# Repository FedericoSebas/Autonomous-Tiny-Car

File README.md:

# Self-Driving Car Project

Hello there, this project is now in v1.0.0. We have developed the initial idea and made significant progress.

## Project Overview

This project is about a self-driving car that uses a PC and an ESP32CAM mounted on a tiny car. The video from the ESP32CAM is processed on the PC using Python, NumPy, and OpenCV to measure the curve of a path. The curve data is then sent to a MQTT broker, which forwards it to the ESP32CAM. The ESP32CAM uses this curve data to control the car's movement using a PID system.

## Key Files

The main logic of the project is contained in two files:

1. `./src-arduino/src/sketch.cpp` lines 1225 to 1242: This part of the code handles the communication with the MQTT broker and the processing of the curve data.

2. `./src-arduino/src/Motor.cpp` lines 40 to 87: This part of the code controls the movement of the car based on the curve data. It uses a PID system to adjust the car's speed and direction based on the curve of the path. After moving the motors, there is a microsecond delay before returning the curve and turn values.

## Requirements

If you want to upload the code to your ESP32CAM, you need to use PlatformIO and be in the ./src-arduino directory. Then, type `pio run` in the command line. This will download all the necessary libraries. After that, type `pio -t upload`, and it will upload the code to your ESP32CAM. If you are not comfortable with PlatformIO, you can extract the entire src-arduino folder and use it in Arduino. Please note that you might need to adjust the library paths in your code if you move it to a different location.

## Future Updates

We are continuously working on improving this project. Stay tuned for future updates!

## Illustrative Content

https://github.com/FedericoSebas/CERTERO-Smart-Car/assets/108437899/04f8dd56-40b6-4fee-bdeb-6901cfbc2fd8

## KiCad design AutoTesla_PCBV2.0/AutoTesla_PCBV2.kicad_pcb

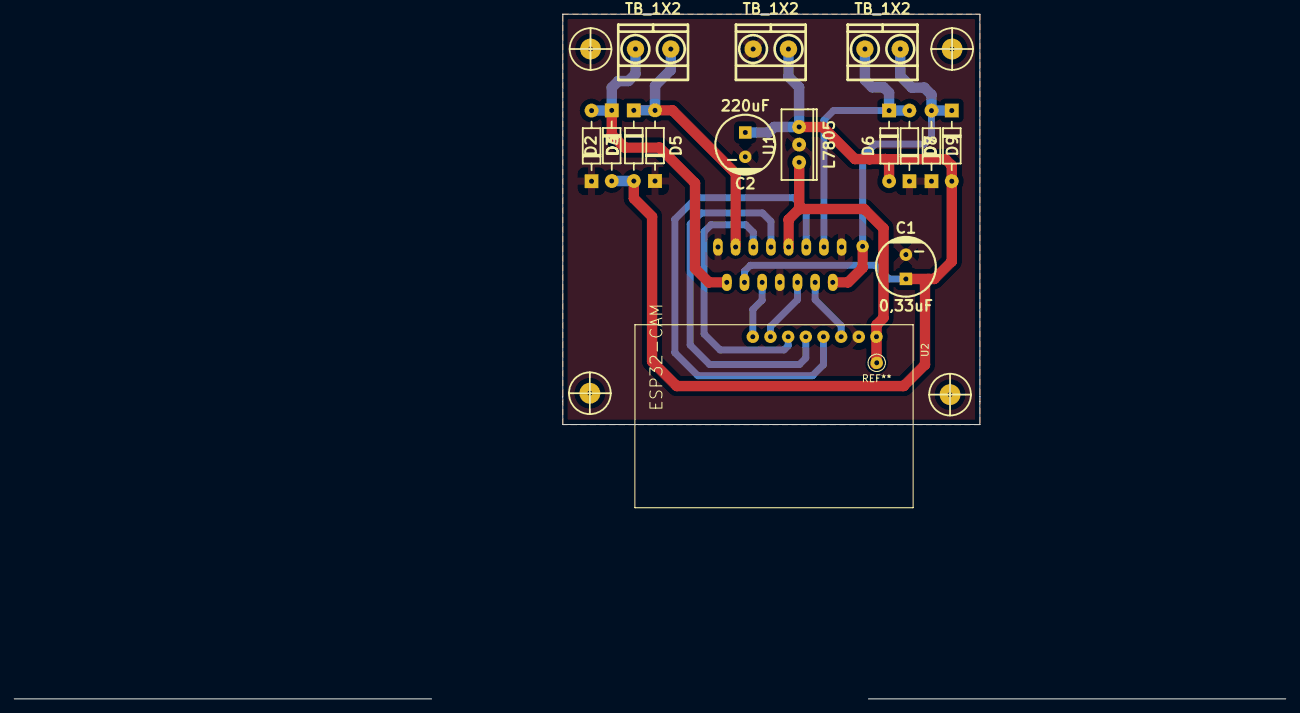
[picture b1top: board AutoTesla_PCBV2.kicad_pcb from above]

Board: 2 copper layers, 60.0 x 59.0 mm, 20 parts (1 on the bottom side), 13 nets.

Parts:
C1: 0,33uF; CAP_ELEC_8x11.5mm
C2: 220uF; CAP_ELEC_8x11.5mm
D2, D3, D4, D5, D6, D7, D8, D9: D; DO-41
H1, H2, H3, H4: Mounting_Hole; hole_3mm
J1, J2, J3: TB_1X2; BORNERA2_AZUL
U1: L7805; TO-220
U2: ESP32-CAM
U3: L298HN; TO127P2020X500X2100-15

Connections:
+5V: U1.3 (OUT), U2.P$1 (5V), U3.9 (Vss)
+6V: C1.1, C2.1, D2.1 (K), D4.1 (K), D6.1 (K), D8.1 (K), J1.1, U1.1 (IN), U3.4 (Vs)
/EnA: U2.P$8 (IO4), U3.6 (EnA)
/EnB: U2.P$4 (IO13), U3.11 (EnB)
/IN1: U2.P$6 (IO14), U3.5 (IN1)
/IN2: U2.P$5 (IO15), U3.7 (IN2)
/IN3: U2.P$7 (IO2), U3.10 (IN3)
/IN4: U2.P$3 (IO12), U3.12 (IN4)
/OUT1: D2.2 (A), D3.1 (K), J3.2, U3.2 (OUT1)
/OUT2: D4.2 (A), D5.1 (K), J3.1, U3.3 (OUT2)
/OUT3: D6.2 (A), D7.1 (K), J2.2, U3.13 (OUT3)
/OUT4: D8.2 (A), D9.1 (K), J2.1, U3.14 (OUT4)
GND: C1.2, C2.2, D3.2 (A), D5.2 (A), D7.2 (A), D9.2 (A), J1.2, U1.2 (GND), U2.P$2 (GND), U3.1 (SENSE_A), U3.8 (GND), U3.15 (SENSE_B)

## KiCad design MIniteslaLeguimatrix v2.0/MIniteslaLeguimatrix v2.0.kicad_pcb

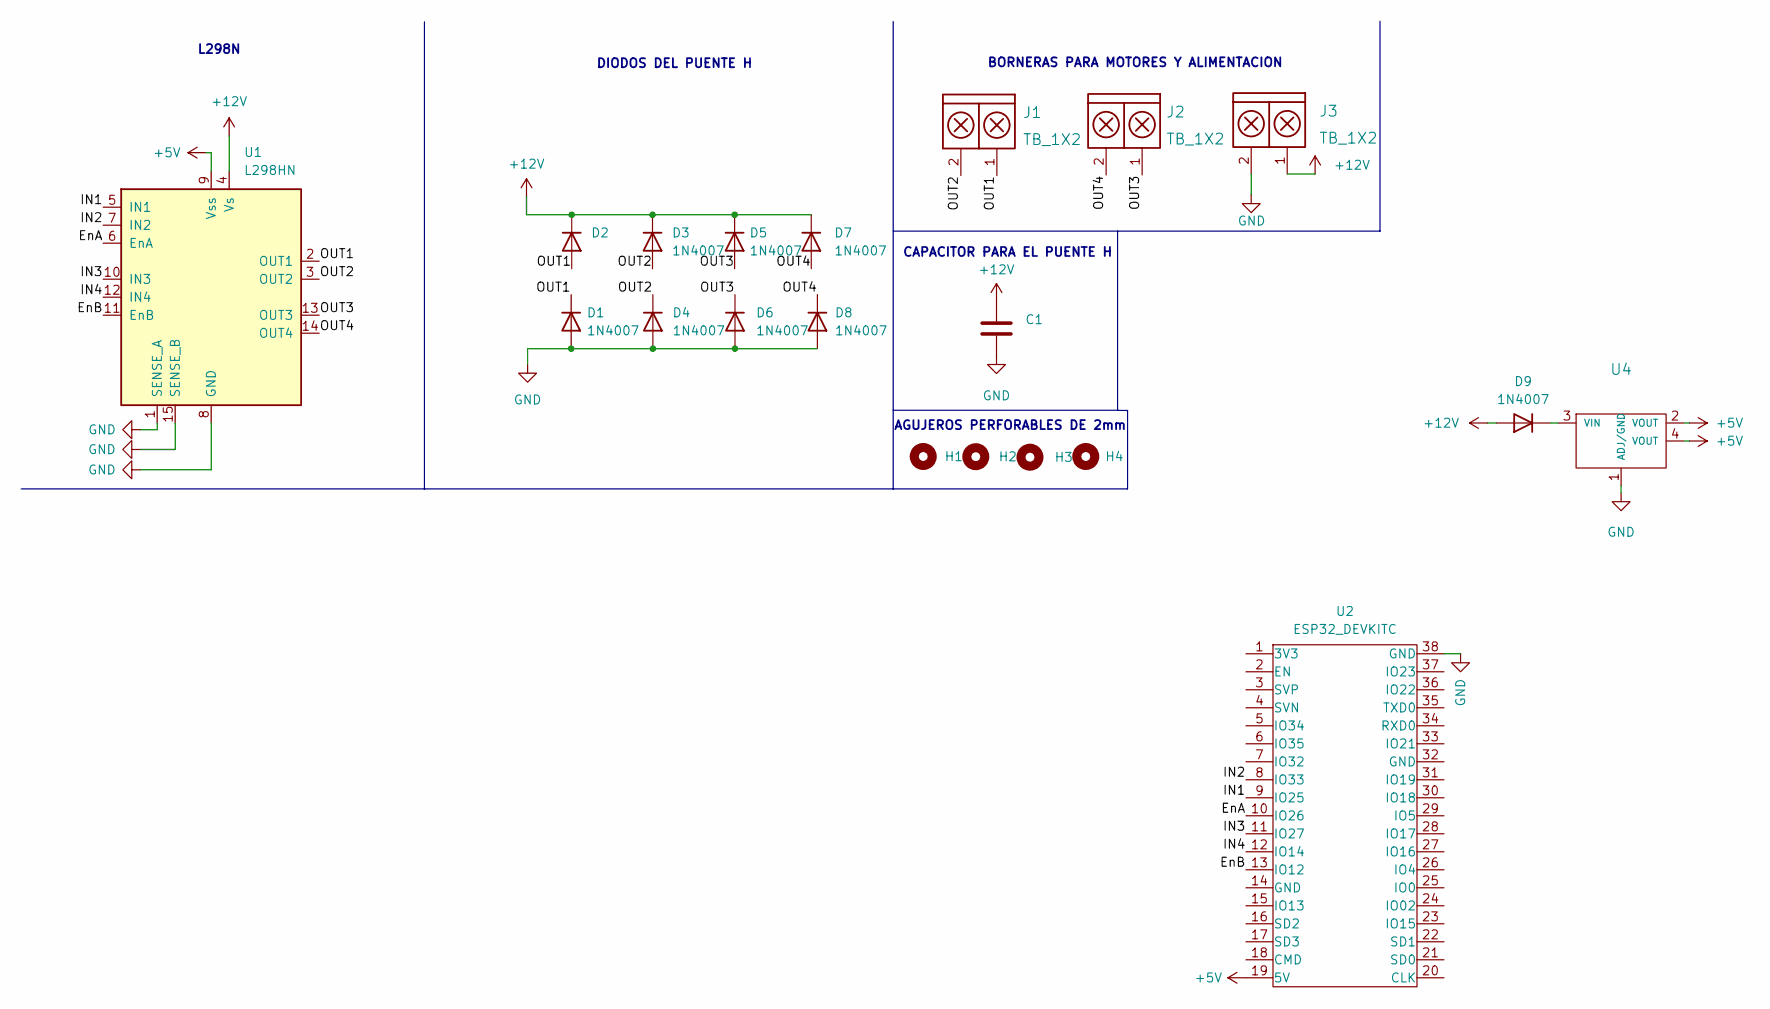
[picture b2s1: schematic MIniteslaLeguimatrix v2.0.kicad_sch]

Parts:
C1: (no value)
D1, D3, D4, D5, D6, D7, D8, D9: 1N4007
D2: (no value)
H1, H2, H3, H4: Mounting_Hole; Tornillo_M3_8mm
J1, J2, J3: TB_1X2; BORNERA2_AZUL
U1: L298HN; TO-220-15_P2.54x2.54mm_StaggerOdd_Lead4.58mm_Vertical
U2: ESP32_DEVKITC
U4: (no value)

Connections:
+5V: U1.9 (Vss), U2.19 (5V), U4.2 (VOUT), U4.4 (VOUT)
+12V: C1.1, D2.1 (K), D3.1 (K), D5.1 (K), D7.1 (K), D9.2 (A), J3.1, U1.4 (Vs)
/EnA: U1.6 (EnA), U2.10 (IO26)
/EnB: U1.11 (EnB), U2.13 (IO12)
/IN1: U1.5 (IN1), U2.9 (IO25)
/IN2: U1.7 (IN2), U2.8 (IO33)
/IN3: U1.10 (IN3), U2.11 (IO27)
/IN4: U1.12 (IN4), U2.12 (IO14)
/OUT1: D1.1 (K), D2.2 (A), J1.1, U1.2 (OUT1)
/OUT2: D3.2 (A), D4.1 (K), J1.2, U1.3 (OUT2)
/OUT3: D5.2 (A), D6.1 (K), J2.1, U1.13 (OUT3)
/OUT4: D7.2 (A), D8.1 (K), J2.2, U1.14 (OUT4)
GND: C1.2, D1.2 (A), D4.2 (A), D6.2 (A), D8.2 (A), J3.2, U1.1 (SENSE_A), U1.8 (GND), U1.15 (SENSE_B), U2.38 (GND), U4.1 (ADJ/GND)
unnamed: D9.1 (K), U4.3 (VIN)

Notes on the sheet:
L298N
DIODOS DEL PUENTE H
BORNERAS PARA MOTORES Y ALIMENTACION
AGUJEROS PERFORABLES DE 2mm
CAPACITOR PARA EL PUENTE H

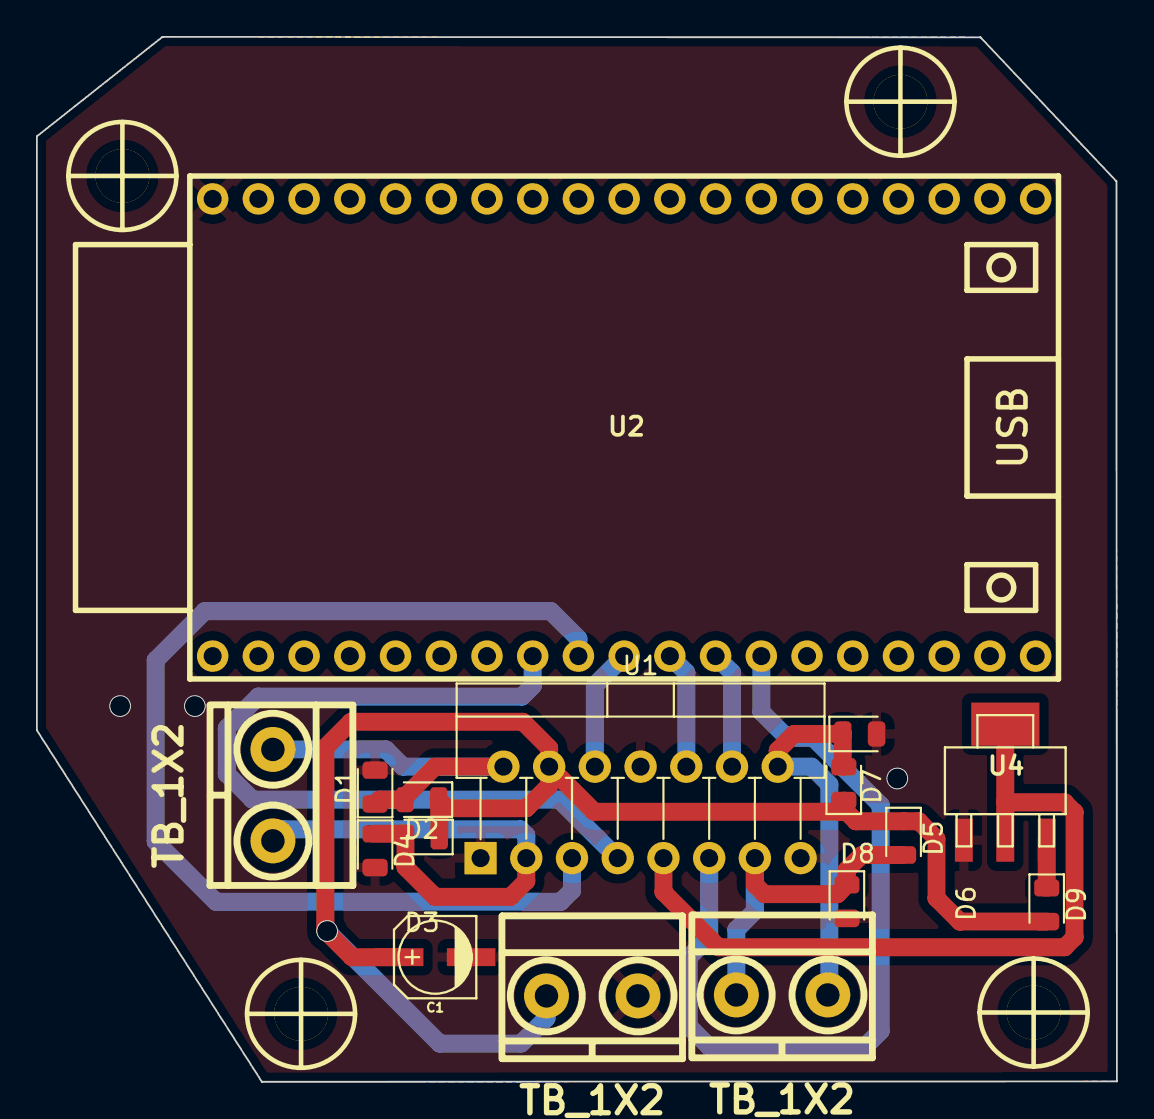
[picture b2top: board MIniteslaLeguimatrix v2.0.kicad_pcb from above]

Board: 2 copper layers, 60.0 x 58.1 mm, 20 parts (0 on the bottom side), 14 nets.

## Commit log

2022-08-19 introduction
2022-08-19 first schematic and pcb desing
2022-08-22 new pcb
2022-08-23 first 3d design
2022-08-26 pcb and schematic maked by Virues
2022-08-30 first code sample
2022-09-01 i cant compile MainModule.py but when i compile LaneModule.py it works, i dont know what to change
2022-09-01 i resolved the problem but when i publish the variable turn the message stills the same as the first value send, no matter the changes of the variable turn makes.In function Mqtt()
2022-09-02 it seems that the problem is solved, is needed to compile only MqttModule.py
2022-09-05 i removed mainModule and i put its whole code on WebcamModule, and the compilation process works faster
2022-09-10 i improved the moudulation of the workspace putting back mainModule. Also i added colorPicker for change black and white image, then you must to hardcode the values in lanemodule, the same for Points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
2022-09-11 i have been working in the arduino code for the esp32, it is not completed at all but works fine, the RC and AUTONOMY mode works on mqtt, pay attention to the topics
2022-09-14 git commit
2022-09-18 i added the first part of the network algorithm
2022-09-26 i modify the first step and works well, now im focus on second step
2022-09-26 i cleaned some things
2022-10-02 i added tools for the server
2022-10-02 i resolved some errors
2022-10-02 i resolved some errors again
2022-10-02 update the enviroment port
2022-10-02 env on gitignore
2022-10-03 using mongo db
2022-10-03 i added a new title
2022-10-03 resolved error gitignore
2022-10-17 i added in src-arduino the web server using esp32cam.It also use mqtt
2022-10-21 i changed the name of the src file
2022-10-23 Now the l298 control is only for in pins, the en pins have a jumper
2022-10-26 i cleaned just a little bit el code and also there was a problem about the mqtt servers, now is solved
2022-10-26 there was a problem about the mqtt servers in arduino, now is solved
2022-10-29 i added some examples in datacollected folder
2022-11-01 i resolved some problems with the mqtt broker in arduino-src
2022-11-08 i uploaded the new designs and i removed some
2022-11-08 i deleted somes pcb designs, i just left the pcb used in this project
2022-11-08 the functionality of the car
2022-11-08 i rename the file
2023-12-18 restore data
